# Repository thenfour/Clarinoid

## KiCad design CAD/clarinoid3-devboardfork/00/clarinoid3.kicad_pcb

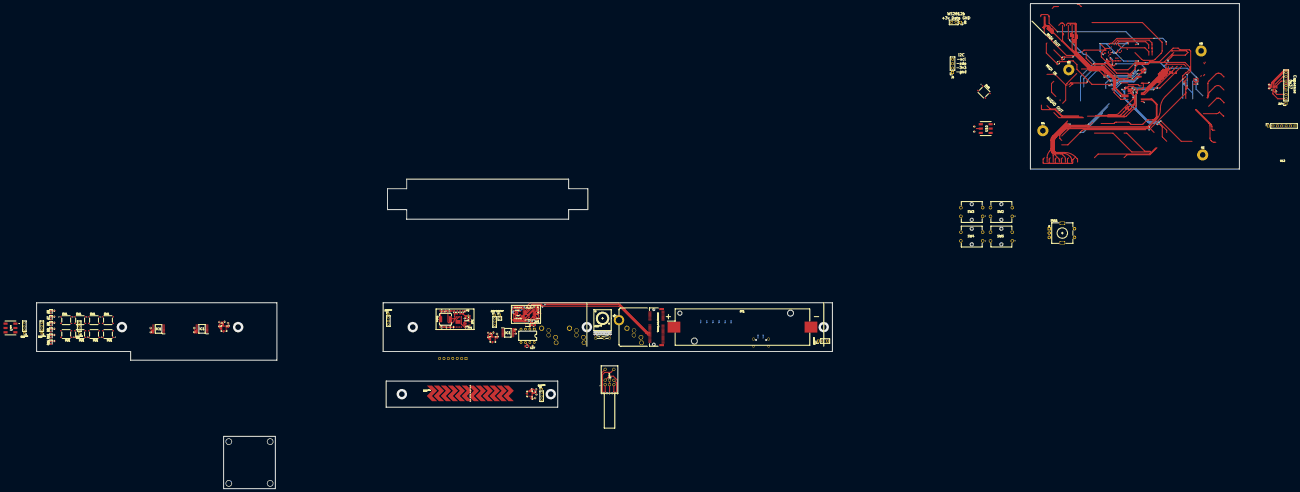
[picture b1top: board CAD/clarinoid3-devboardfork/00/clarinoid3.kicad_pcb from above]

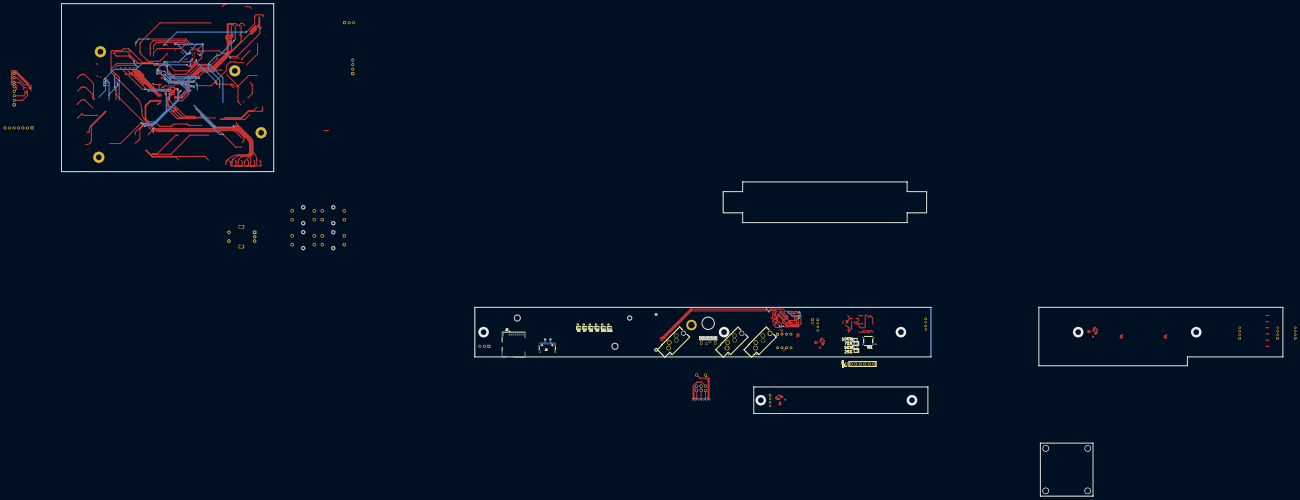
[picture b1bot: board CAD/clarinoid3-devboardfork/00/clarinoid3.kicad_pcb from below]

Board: 2 copper layers, 690.7 x 278.5 mm, 146 parts (24 on the bottom side), 90 nets.

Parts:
BT1: Battery_Cell; BatteryHolder_Keystone_1042_1x18650
C3, C5, C10, C11, C15, C16, C26: 10uF; C_0402_1005Metric
C4, C6, C13, C14, C23, C24, C24#2, C24#3, C25, C25#2, C25#3, C27, C30: 0.1uF; C_0402_1005Metric
C7, C8, C9, C12: 2.2uF; C_0402_1005Metric
C17, C18, C19, C20, C21, C22: 22uF; C_0603_1608Metric
C28: 0.22uF; C_0603_1608Metric
C29: 0.1uF; C_0603_1608Metric
D1: 25%; LED_0805_2012Metric
D2: 50%; LED_0805_2012Metric
D3: 75%; LED_0805_2012Metric
D4: 100%; LED_0805_2012Metric
D5, D5#2, D7, D7#2, D8, D8#2, D9, D9#2, D10, D10#2, D11, D11#2: LED; LED_0603_1608Metric
D6: 1N4148; D_SOD-323
H1: M.2 riser SMTSO2530CTJ; Wurth_9774025151_M2.5_spacer_for_micromod
H2, H3, H4, H5: MountingHole; MountingHole_3.2mm_M3_Pad
IC1, IC1#2, IC1#3: PCA9554APW,118; SOP65P640X110-16N
IC2: Injoinic IP5306 battery charge; SOIC127P599X155-9N
IC4: CY8CMBR3108-LQXIT; QFN50P300X300X60-17N-D
J1: Switchcraft 35RAPC4BV4; SWITCHCRAFT_35RAPC4BV4
J2: XKB_U262-16XN-4BVC11 USB-C recept; USB_C_Receptacle_XKB_U262-16XN-4BVC11
J3: Molex microSD 503398-1892; MOLEX_503398-1892
J5: header_i2c; PinSocket_1x04_P2.54mm_Vertical
J10: MIDI IN; SWITCHCRAFT_35RAPC4BV4
J11: MIDI OUT; SWITCHCRAFT_35RAPC4BV4
J12: SSD1306; PinSocket_1x07_P2.54mm_Vertical
J14: touch_conn_capsense; PinSocket_1x08_P2.54mm_Vertical
L1: 1uH; Inductor_MCS0630-1R0MN2
NT1: NetTie_2; NetTie-2_SMD_Pad0.5mm
R1, R2, R3: 22R; R_0402_1005Metric
R4, R4#2, R4#3, R10, R13, R13#2, R13#3, R14, R14#2, R14#3, R17, R17#2, R17#3, R18, R18#2, R18#3, R40, R41, R43, R44: 10k; R_0402_1005Metric
R5, R6, R34, R34#2, R35, R35#2, R36, R36#2, R37, R37#2, R38, R38#2, R39, R39#2: 470R; R_0402_1005Metric
R7, R8: 5.1k; R_0402_1005Metric
R9: 2R; R_0603_1608Metric
R11: 0.5R; R_0402_1005Metric
R12, R12#2, R12#3: 75k; R_0402_1005Metric
R19: 220R; R_0805_2012Metric
R20, R21: 47R; R_0805_2012Metric
R22: 470R; R_0805_2012Metric
R**: PTR902-2020K-A103
SW1, SW1#2, SW1#3, SW1#4, SW1#5, SW1#6, SW1#7, SW1#8, SW1#9, SW6: SW_Push; XKB switch jlcpcb SW_TS-1187A-B-A-B
SW2, SW3, SW4, SW5: SW_Push; B3F-4055
SW11: RotaryEncoder_Switch; RotaryEncoder_Alps_EC11E-Switch_Vertical_H20mm
U1: PCM5102A; TSSOP-20_4.4x6.5mm_P0.65mm
U3: APCI0136-P001A Teensy_4.0_MicroMod; Teensy_4.0_MicroMod_nospacer
U4, U4#2, U4#3: MPR121, 0x5A; UQFN-20_3x3mm_P0.4mm
U7: TLV75533PDBV; SOT-23-5
U8: 6N138; DIP-8_W7.62mm
U9: WS2812; PinSocket_1x03_P2.54mm_Vertical
U10: Pressure1_0x28_I2C0; ABPMAND001PG2A3
U11: TLV75733PDBV; SOT-23-5
U12: ssd1306_graphic; SSD1306_128x64_approximate
U**: ABPMAND001PG2A3

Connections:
+3V3: C5.1, C6.1, C25.1, C25#2.1, C25#3.1, IC1.16 (VDD), IC1#2.16 (VDD), IC1#3.16 (VDD), IC4.5 (VDDIO), IC4.6 (VDD), J3.4 (VDD_vin), J5.2, J12.2 (VDD), NT1.1, R4.2, R4#2.2, R4#3.2, R13.2, R13#2.2, R13#3.2, R14.2, R14#2.2, R14#3.2, R17.2, R17#2.2, R17#3.2, R18.2, R18#2.2, R18#3.2, R20.2, R22.1, R40.2, R41.2, R43.2, R44.2, U3.2 (3.3v), U4.20 (VDD), U4#2.20 (VDD), U4#3.20 (VDD), U9.3 (+5v), U10.2 (Vs), U11.5 (OUT)
A3v3: C3.1, C4.1, U1.1 (CPVDD), U1.8 (AVDD), U7.5 (OUT)
Batt+: BT1.1 (+), C19.1, L1.2, R11.1
D3v3: C11.2, C14.2, NT1.2, U1.17 (XSMT), U1.20 (DVDD), U7.1 (IN), U7.3 (EN)
ENC_A: SW11.A, U3.42 (41_G1)
ENC_B: SW11.B, U3.44 (42_G2)
ENC_SWITCH: SW11.S1, U3.40 (40_G0)
GEN_LED1: D5.2 (A), D5#2.2 (A), U3.47 (2_PWM1)
GEN_LED2: D7.2 (A), D7#2.2 (A), U3.32 (3_PWM0)
GEN_LED3: D8.2 (A), D8#2.2 (A), U3.10 (4_D0)
GEN_LED4: D9.2 (A), D9#2.2 (A), U3.18 (5_D1)
GEN_LED5: D10.2 (A), D10#2.2 (A), U3.71 (6_G6)
GEN_LED6: D11.2 (A), D11#2.2 (A), U3.69 (9_G7)
GND: BT1.2 (-), C3.2, C4.2, C5.2, C6.2, C9.2, C10.2, C11.1, C12.2, C13.2, C14.1, C15.2, C16.2, C17.2, C18.2, C19.2, C20.2, C21.2, C22.2, C23.2, C24.2, C24#2.2, C24#3.2, C25.2, C25#2.2, C25#3.2, C26.2, C27.2, C28.2, C29.2, C30.2, IC1.1 (A0), IC1.2 (A1), IC1.3 (A2), IC1.8 (VSS), IC1#2.1 (A0), IC1#2.2 (A1), IC1#2.3 (A2), IC1#2.8 (VSS), IC1#3.1 (A0), IC1#3.2 (A1), IC1#3.3 (A2), IC1#3.8 (VSS), IC2.9 (PWR-GND), IC4.7 (VSS), IC4.17 (EP), J1.1 (S-GND), J2.A1 (GND), J2.A12 (GND), J2.B1 (GND), J2.B12 (GND), J2.S1 (SHIELD), J3.6 (VSS_gnd), J3.9 (VSS), J3.P1 (SHIELD), J3.P2 (SHIELD), J3.P3 (SHIELD), J3.P4 (SHIELD), J5.1, J11.1 (S-GND), J12.1 (GND), J14.1, R7.1, R8.1, R12.2, R12#2.2, R12#3.2, R34.2, R34#2.2, R35.2, R35#2.2, R36.2, R36#2.2, R37.2, R37#2.2, R38.2, R38#2.2, R39.2, R39#2.2, SW1#9.1, SW2.1, SW3.1, SW4.1, SW5.1, SW6.2, SW11.C, SW11.S2, U1.9 (AGND), U1.10 (DEMP), U1.11 (FLT), U1.16 (FMT), U1.19 (DGND), U3.1 (GND), U3.7 (GND), U3.33 (GND), U3.36 (GND), U3.39 (GND), U3.45 (GND), U3.75 (GND), U4.4 (ADDR), U4.6 (VSS), U4#2.4 (ADDR), U4#2.6 (VSS), U4#3.4 (ADDR), U4#3.6 (VSS), U7.2 (GND), U8.5 (GND), U9.1 (gnd), U10.1 (GND), U11.2 (GND)
I2C_SCL: IC1.14 (SCL), IC1#2.14 (SCL), IC1#3.14 (SCL), IC4.15 (I2C_SCL), J5.4, R14.1, R14#2.1, R14#3.1, R17.1, R17#2.1, R17#3.1, R40.1, R44.1, U3.14 (19_SCL_A5), U4.2 (SCL), U4#2.2 (SCL), U4#3.2 (SCL), U10.6 (SCL)
I2C_SDA: IC1.15 (SDA), IC1#2.15 (SDA), IC1#3.15 (SDA), IC4.14 (I2C_SDA), J5.3, R13.1, R13#2.1, R13#3.1, R18.1, R18#2.1, R18#3.1, R41.1, R43.1, U3.12 (18_SDA_A4), U4.3 (SDA), U4#2.3 (SDA), U4#3.3 (SDA), U10.5 (SDA)
I2S_BCK: R3.1, U3.50 (21_BCLK_A7)
I2S_DIN: R2.1, U3.56 (7_AUD_OUT)
I2S_LRCK: R1.1, U3.52 (20_LRCLK_A6)
unnamed: C7.1, U1.2 (CAPP)
unnamed: C7.2, U1.4 (CAPM)
unnamed: C8.1, U1.5 (VNEG)
unnamed: C8.2, U1.3 (CPGND)
unnamed: C9.1, J1.2 (Tip), R5.2
unnamed: C10.1, C13.1, U1.18 (LDOO)
unnamed: C12.1, J1.4 (Ring), R6.2
unnamed: C15.1, R9.2
unnamed: C18.1, IC2.6 (BAT), R11.2
unnamed: C24.1, C24#2.1, C24#3.1, U4.5 (VREG), U4#2.5 (VREG), U4#3.5 (VREG)
unnamed: C30.1, IC4.4 (VCC)
unnamed: D1.1 (K), D2.2 (A), D3.1 (K), D4.2 (A), IC2.4 (LED3)
unnamed: D1.2 (A), D2.1 (K), IC2.2 (LED1)
unnamed: D3.2 (A), D4.1 (K), IC2.3 (LED2)
unnamed: D5.1 (K), D5#2.1 (K), R34.1, R34#2.1
unnamed: D6.1 (K), R19.2, U8.2 (C1)
unnamed: D6.2 (A), J10.2, U8.3 (C2)
unnamed: D7.1 (K), D7#2.1 (K), R35.1, R35#2.1
unnamed: D8.1 (K), D8#2.1 (K), R36.1, R36#2.1
unnamed: D9.1 (K), D9#2.1 (K), R37.1, R37#2.1
unnamed: D10.1 (K), D10#2.1 (K), R38.1, R38#2.1
unnamed: D11.1 (K), D11#2.1 (K), R39.1, R39#2.1
unnamed: IC1.4 (IO0), IC1#2.4 (IO0), IC1#3.4 (IO0), SW2.2
unnamed: IC1.5 (IO1), IC1#2.5 (IO1), IC1#3.5 (IO1), SW3.2
unnamed: IC1.6 (IO2), IC1#2.6 (IO2), IC1#3.6 (IO2), SW4.2
unnamed: IC1.7 (IO3), IC1#2.7 (IO3), IC1#3.7 (IO3), SW5.2
unnamed: IC2.5 (KEY), R10.1
unnamed: IC2.7 (SW-inductor), L1.1
unnamed: IC4.1 (CS0/PS0), J14.2
unnamed: IC4.2 (CS1/PS1), J14.3
unnamed: IC4.8 (CS4/GPO0), J14.6
unnamed: IC4.9 (CS5/GPO1), J14.7
unnamed: IC4.11 (CS7/GPO3/SH), J14.8
unnamed: IC4.12 (CS2/GUARD), J14.4
unnamed: IC4.13 (CS3), J14.5
unnamed: J2.A5 (CC), R8.2
unnamed: J2.B5 (VCONN), R7.2
unnamed: J10.4 (Ring), R19.1
unnamed: J11.2, R21.1
unnamed: J11.4 (Ring), R20.1
unnamed: U4.8 (ELE0), U4#2.8 (ELE0), U4#3.8 (ELE0)
unnamed: U4.9 (ELE1), U4#2.9 (ELE1), U4#3.9 (ELE1)
unnamed: U4.10 (ELE2), U4#2.10 (ELE2), U4#3.10 (ELE2)
unnamed: U4.11 (ELE3), U4#2.11 (ELE3), U4#3.11 (ELE3)
unnamed: U4.12 (LED0/ELE4), U4#2.12 (LED0/ELE4), U4#3.12 (LED0/ELE4)
unnamed: U4.13 (LED1/ELE5), U4#2.13 (LED1/ELE5), U4#3.13 (LED1/ELE5)
unnamed: R1.2, U1.15 (LRCK)
unnamed: R2.2, U1.14 (DIN)
unnamed: R3.2, U1.13 (BCK)
unnamed: R4.1, R4#2.1, R4#3.1, U4.1 (~IRQ), U4#2.1 (~IRQ), U4#3.1 (~IRQ)
unnamed: R5.1, U1.6 (OUTL)
unnamed: R6.1, U1.7 (OUTR)
unnamed: R10.2, SW1#9.2
unnamed: R12.1, R12#2.1, R12#3.1, U4.7 (REXT), U4#2.7 (REXT), U4#3.7 (REXT)
unnamed: SW6.1, U3.11 (PROGRAM)
OLED_CS: J12.7 (CS), U3.55 (10_SPI_CS)
OLED_DC: J12.6 (DC), U3.46 (43_G3)
OLED_RES: J12.5 (RES), U3.48 (44_G4)
SDIO_CLOCK: J3.5 (CLK), U3.60 (36_SDIO_CLK)
SDIO_CS: J3.2 (SS_CS_CD/DAT3^2), U3.70 (39_SDIO_DATA3)
SDIO_MISO: J3.7 (MISO_DAT0), U3.64 (35_SDIO_DATA0)
SDIO_MOSI: J3.3 (MOSI_CMD), U3.62 (37_SDIO_CMD)
SPI0_MOSI: J12.4 (SDA), U3.59 (11_SPI_SDO)
SPI0_SCK: J12.3 (SCK), U3.57 (13_SPI_SCK)
Supply+5v: C17.1, C20.1, C21.1, C22.1, C23.1, C26.1, C27.1, C28.1, C29.1, IC2.8 (VOUT), U3.9 (VUSB), U8.8 (VCC), U11.1 (IN), U11.3 (EN)
T00 MIDI IN: R22.2, U3.19 (0_RX1), U8.6 (VO2)
T01=MIDI OUT: R21.2, U3.17 (1_TX1)
USB data in +: J2.A6 (D+), U3.3 (D+)
USB data in -: J2.A7 (D-), U3.5 (D-)
USB_Vin5v: C16.1, IC2.1 (VIN), J2.A4 (VBUS), J2.A9 (VBUS), J2.B4 (VBUS), J2.B9 (VBUS), R9.1
WS2812_DATA: U3.22 (17_TX2_A3), U9.2 (Data)

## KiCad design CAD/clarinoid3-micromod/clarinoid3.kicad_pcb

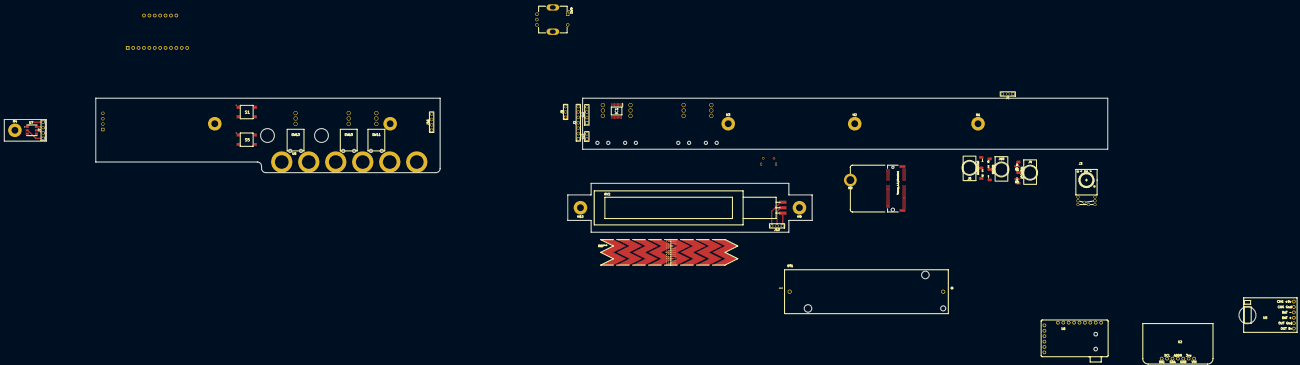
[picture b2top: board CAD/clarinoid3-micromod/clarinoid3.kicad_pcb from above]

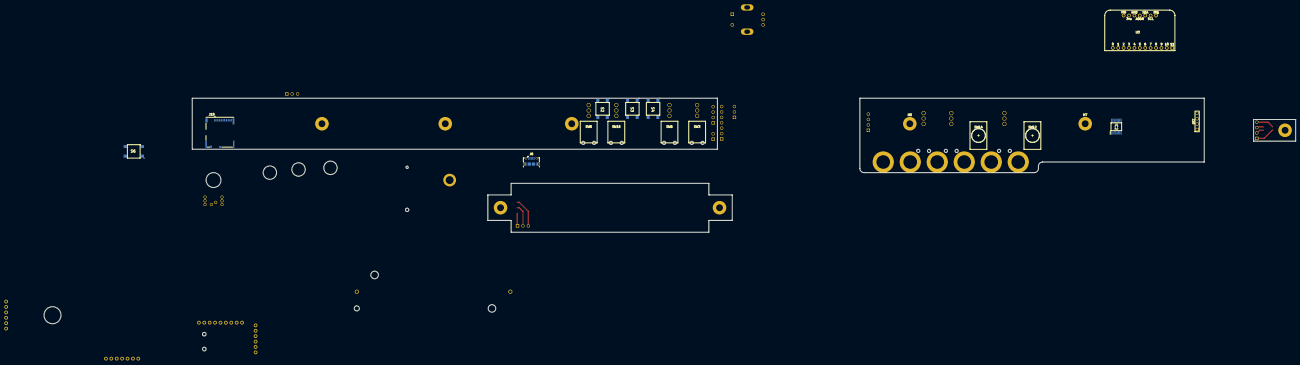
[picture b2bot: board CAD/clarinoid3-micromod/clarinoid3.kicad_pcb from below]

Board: 2 copper layers, 519.0 x 63.0 mm, 53 parts (17 on the bottom side), 14 nets.

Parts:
BT1: Battery_Cell; KEYSTONE_1043
H1: rh_h1; MountingHole_3.2mm_M3_Pad
H2: rh_h2; MountingHole_3.2mm_M3_Pad
H3: rh_h3; MountingHole_3.2mm_M3_Pad
H4: breath_h1; MountingHole_3.2mm_M3_Pad
H5: lh_h1; MountingHole_3.2mm_M3_Pad
H7: lh_h2; MountingHole_3.2mm_M3_Pad
H8: micromod_spacer; Wurth_9774025151_M2.5_spacer_for_micromod
H9: pitch_h1; MountingHole_3.2mm_M3_Pad
H10: pitch_h2; MountingHole_3.2mm_M3_Pad
IC1, IC2: PCA9554APW,118; SOP65P640X110-16N
J1: LEDHdr; solder point DIP 1x3
J2: OLEDHdr; solder point DIP 1x7
J3: StereoPot_SW; Bourns_POT_PTR902-2020K-A103_PANEL
J4: MIDIOut; Switchcraft_35RAPC4BH3_3.5mm_female_jack_nosw_downfacing
J5: AudioOut; Switchcraft_35RAPC4BH3_3.5mm_female_jack_nosw_downfacing
J7: BREATHI2CHdr; solder point DIP 1x4
J8: USB_B_Micro; USB_Micro-B_Amphenol_10118194_Horizontal
J9: RH_PitchHdr; solder point DIP 1x3
J10: pitch_pitchhdr; solder point DIP 1x3
J12: RHI2CHdr; solder point DIP 1x4
J13: RHencHdr; solder point DIP 1x2
J16: LHI2CHdr; solder point DIP 1x4
J18: MIDIin; Switchcraft_35RAPC4BH3_3.5mm_female_jack_nosw_downfacing
J19: Molex microSD 503398-1892; MOLEX_503398-1892
J20: LH-BREATHI2CHdr; solder point DIP 1x4
R1, R2: 47; R_0603_1608Metric
RV2: PITCH; MAT060-B100K-231-A01
S1: LHxv1; B3FS-1000P
S2: RHxv1; B3FS-1000P
S3: RHxv2; B3FS-1000P
S4: RHxv3; B3FS-1000P
S5: LHxv2; B3FS-1000P
S6: charge_ind_btn; B3FS-1000P
SW3: RHx1; MB2511S2G45
SW5: RHx2; MB2511S2G45
SW6: RHx3; MB2511S2G45
SW9: Rotary_Encoder_Switch; Bourns_ENC_PEC11R-4215F-S0024
SW10: LHx1; MB2511S2G45
SW11: LHx2; MB2511S2G45
SW12: LHback; MB2511S4W01-BC
SW13: LHx3; MB2511S2G45
SW14: LHok; MB2511S4W01-BC
SW15: RHx4; MB2511S2G45
U1: Teensy_4.0_MicroMod; Teensy_4.0_MicroMod_nospacer
U2: AdafruitMPR121; MPR121_hdr_0keys_copy
U3: AdafruitMPR121; MPR121_hdr_12keys
U5: MH-CD42; MH-CD42_flip_window
U6: PCM5102; HILETGOPCM5102
U7: HoneywellABPMAND001PG2A3; SON160P500X500X140-6N
U8: octave_keys; CLARINOID_M6_6OCTAVES

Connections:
+3V3: J7.1, J10.1, J16.4, J20.1, RV2.1, U2.19 (Vin), U3.19 (Vin), U7.2 (Vs)
GND: J7.4, J10.3, J16.3, J20.4, RV2.3, S1.1 (COM_1), S2.3 (NO_1), S3.3 (NO_1), S4.3 (NO_1), S5.1 (COM_1), SW3.2, SW5.2, SW6.2, SW9.S2, SW10.2, SW11.2, SW13.2, SW15.2, U2.17 (GND), U3.17 (GND), U7.1 (GND)
unnamed: J10.2, RV2.2
unnamed: J19.6 (VSS), J19.9 (VSS)
unnamed: J19.P1 (SHIELD), J19.P2 (SHIELD), J19.P3 (SHIELD), J19.P4 (SHIELD)
unnamed: U3.4, U8.6
unnamed: U3.5, U8.5
unnamed: U3.6, U8.4
unnamed: U3.7, U8.3
unnamed: U3.8, U8.2
unnamed: U3.9, U8.1
unnamed: U3.16 (Addr), U3.18 (3vo)
i2c_scl: J7.3, J16.1, J20.3, U2.14 (SCL), U3.14 (SCL), U7.6 (SCL)
i2c_sda: J7.2, J16.2, J20.2, U2.15 (SDA), U3.15 (SDA), U7.5 (SDA)
